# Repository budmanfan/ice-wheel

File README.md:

# ice-wheel

### Orientation visualizer
[Description on pjrc.com](https://www.pjrc.com/store/prop_shield.html)

- Download **File > Examples > NXPMotionSense > Orientation** to teensy
- Install [Processing](https://processing.org/download/?processing)
- Run `IceWheelOrientation.pde` with the correct port where the teensy streams

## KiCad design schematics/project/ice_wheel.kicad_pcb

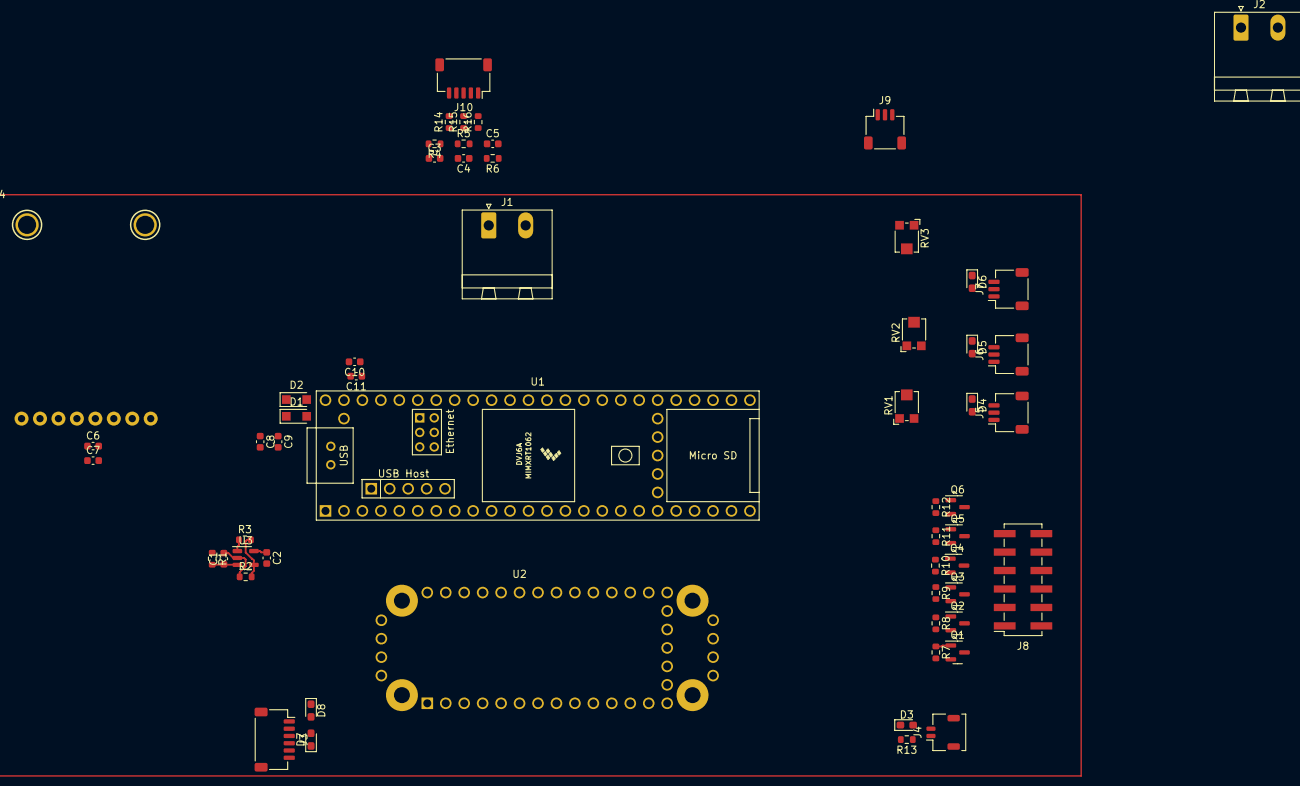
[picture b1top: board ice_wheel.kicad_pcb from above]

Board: 2 copper layers, 58 parts (0 on the bottom side), 45 nets.

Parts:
C1: C; C_0603_1608Metric
C2, C7, C8, C10: 100nF 10V; C_0603_1608Metric
C3, C4, C5: 10nF 10V; C_0603_1608Metric
C6, C9, C11: 1uF 10V; C_0603_1608Metric
D1, D2: PMEG40T20ER; Nexperia_CFP3_SOD-123W
D3, D4, D5, D6, D7, D8: D3V3S1U2LP1610-7; D_0603_1608Metric_Pad1.05x0.95mm_HandSolder
J1, J2: Conn_01x02; PhoenixContact_MSTBA_2,5_2-G-5,08_1x02_P5.08mm_Horizontal
J3: Conn_01x06; JST_SH_SM06B-SRSS-TB_1x06-1MP_P1.00mm_Horizontal
J4: Conn_01x02; JST_SHL_SM02B-SHLS-TF_1x02-1MP_P1.00mm_Horizontal
J5, J6, J7, J9: Conn_01x03; JST_SH_SM03B-SRSS-TB_1x03-1MP_P1.00mm_Horizontal
J8: Conn_02x06_Odd_Even; PinSocket_2x06_P2.54mm_Vertical_SMD
J10: Conn_01x05; JST_SH_SM05B-SRSS-TB_1x05-1MP_P1.00mm_Horizontal
Q1, Q2, Q3, Q4, Q5, Q6: BSS123; SOT-23
R1, R2, R3, R13: R; R_0603_1608Metric
R4, R5, R6: 10k; R_0603_1608Metric
R7, R8, R9, R10, R11, R12: 1k; R_0603_1608Metric
R14, R15, R16: 6.2k; R_0603_1608Metric
RV1, RV2, RV3: TC33X-1-203E; Potentiometer_Bourns_TC33X_Vertical
U1: Teensy4.1; Teensy41
U2: PropShieldMotionSens; Prop Shield Motion Sens
U3: OPA320xxDBV; SOT-23-5
U4: Adafruit_Bluefruit_LE_UART_Friend

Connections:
+3V3: C10.1, C11.1, J4.1, J5.1, J6.1, J7.1, RV1.1, RV2.1, RV3.1, U1.15 (3V3), U1.46 (3V3), U2.26 (3Vpower), U2.30 (3Vpower)
+5F: D1.2 (A), U1.49 (VUSB)
+5P: D2.2 (A), J1.1, U1.48 (VIN)
+5V: C2.1, C6.1, C7.1, C8.1, C9.1, D1.1 (K), D2.1 (K), J10.5, U2.28 (5VPower), U3.5 (V+), U4.4 (5V_Supply)
+48V: J2.1, J8.12, Q6.3 (D)
/Misc/5V_Speaker: J3.5, U2.41 (5VPower)
/Misc/AGND: J3.6, U2.27 (AGND)
/Misc/AMP_EN: J3.3, U2.7 (AMP_EN)
/Misc/AudioIN: J3.4, U2.33 (AudioIN)
/Misc/Speaker+: D8.2 (A2), J3.1, U2.39 (Speaker+)
/Misc/Speaker-: D7.2 (A2), J3.2, U2.40 (Speaker-)
/Misc/footpad_a: D3.2 (A2), J4.2, R13.1, U1.36 (14_A0_TX3_SPDIF_OUT)
/Misc/poti_IN_a0: D4.2 (A2), J5.2, RV1.2
/Misc/poti_IN_a1: D5.2 (A2), J6.2, RV2.2
/Misc/poti_IN_a2: D6.2 (A2), J7.2, RV3.2
/Motor Controller/Hall1: C3.1, R4.2, R14.1
/Motor Controller/Hall2: C4.1, R5.2, R15.1
/Motor Controller/Hall3: C5.1, R6.2, R16.1
/Motor Controller/cruise_IN: J8.7, Q4.3 (D)
/Motor Controller/hiPoBreak_IN: J8.11, Q6.2 (S)
/Motor Controller/lowPoBreak_IN: J8.9, Q5.3 (D)
/Motor Controller/reverse_IN: J8.1, Q1.3 (D)
/Motor Controller/speed_fast_IN: J8.3, Q2.3 (D)
/Motor Controller/speed_slow_IN: J8.5, Q3.3 (D)
/Motor Controller/throttle_a: R3.1, U3.1
/Prop Shield/CS: U1.12 (10_CS_MQSR), U2.8 (CS)
/Prop Shield/IRQ: U1.4 (2_OUT2), U2.4 (IRQ)
/Prop Shield/MISO: U1.14 (12_MISO_MQSL), U2.13 (MISO)
/Prop Shield/MOSI: U1.13 (11_MOSI_CTX1), U2.14 (MOSI)
/Prop Shield/SCK: U1.35 (13_SCK_LED), U2.15 (SCK)
/Prop Shield/SCL: U1.41 (19_A5_SCL), U2.21 (SCL)
/Prop Shield/SDA: U1.40 (18_A4_SDA), U2.20 (SDA)
GND: C1.2, C2.2, C3.2, C4.2, C5.2, C6.2, C7.2, C8.2, C9.2, C10.2, C11.2, D3.1 (A1), D4.1 (A1), D5.1 (A1), D6.1 (A1), D7.1 (A1), D8.1 (A1), J1.2, J5.3, J6.3, J7.3, J9.3, J10.1, R2.1, R4.1, R5.1, R6.1, R13.2, RV1.3, RV2.3, RV3.3, U1.1 (GND), U1.34 (GND), U1.47 (GND), U1.52 (GND), U1.58 (GND), U1.59 (GND), U1.64 (GND), U2.1 (GND), U2.2 (GND), U2.3 (GND), U2.5 (GND), U2.6 (GND), U2.10 (GND), U2.11 (GND), U2.12 (GND), U2.16 (GND), U2.17 (GND), U2.18 (GND), U2.19 (GND), U2.22 (GND), U2.23 (GND), U2.24 (GND), U2.25 (GND), U2.29 (GND), U2.31 (GND), U2.32 (GND), U2.37 (GND), U2.38 (GND), U3.2 (V-), U4.2 (GND)
GNDPWR: J2.2, J8.2, J8.4, J8.6, J8.8, J8.10, Q1.2 (S), Q2.2 (S), Q3.2 (S), Q4.2 (S), Q5.2 (S)
unnamed: C1.1, R1.2, U3.3 (+)
unnamed: Q1.1 (G), R7.1
unnamed: Q2.1 (G), R8.1
unnamed: Q3.1 (G), R9.1
unnamed: Q4.1 (G), R10.1
unnamed: Q5.1 (G), R11.1
unnamed: Q6.1 (G), R12.1
unnamed: R2.2, R3.2, U3.4 (-)
unnamed: J10.4, R14.2
unnamed: J10.3, R15.2
unnamed: J10.2, R16.2

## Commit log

2021-11-25 Create schematics
2021-12-01 Orientation visualizer docs
2021-12-12 First shitty draft
2021-12-30 Probably wrong op-amp.
    @budmanfan select correct opv
2022-04-23 Better simulation/testboard is like this
2022-04-23 IO motor controller
2022-04-23 bit more info
2022-04-26 Inital commit PCB project
2022-04-26 Initial commit PCB project
2022-05-03 some motorcontroller info
2022-05-05 heavyside measurements
2022-05-06 new measurements
2022-05-06 add matlab files
2022-05-07 much work
2022-05-07 Structure of schematics
2022-05-09 first working sim
2022-05-09 add gif of sim
2022-05-11 First steps with kicad structure -> kinda sucks
2022-05-12 added cad pics
2022-05-16 some progress, dust slowly clears
2022-05-20 added images
2022-05-24 added a LOT of docs
2022-05-24 added kiCAD files
2022-05-24 added datasheet
2022-05-24 small progress, angsthasen
2022-05-28 replaced the motherflippin spaces in file names
2022-05-29 Adding separate library, BT Module
2022-06-03 much sophisticated work
2022-06-09 analysis on laptop
2022-09-26 random commit
